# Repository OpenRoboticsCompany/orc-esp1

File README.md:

ESP8266 Development Board
=========================

Front:

Back:

This board provides power, GPIO, and Micro SD to the commonly-available
ESP8266 wifi modules. This first revision is intended for internal use
at Open Robotics Company, but may find it's way out to the world also.

Built using [KiCad EDA](http://kicad.org/)

PCB images courtesy of OSHPark's magical preview.

Important Build Notes
---------------------

Please note that we used a nightly dev build of KiCad for this project.
You cannot open the files in the current stable version (4.0.5 as of this
writing).  We used *kicad-r7402.f631ae2-x86_64* on Windows. It's possible
that later versions will open the files, but because nightly builds are
always changing, you never know!

Copyright
---------

Designed by [Aaron Kondziela](https://aaronkondziela.com).
Copyright 2017 [Open Robotics Company LLC](https://openrobotics.company)

If any files (datasheets, etc) have been included here that are not
our original work, they are (obviously) the copyright of their respective
authors.

License
-------

This work is licensed under a Creative Commons Attribution-ShareAlike 4.0 International License.

https://creativecommons.org/licenses/by-sa/4.0/

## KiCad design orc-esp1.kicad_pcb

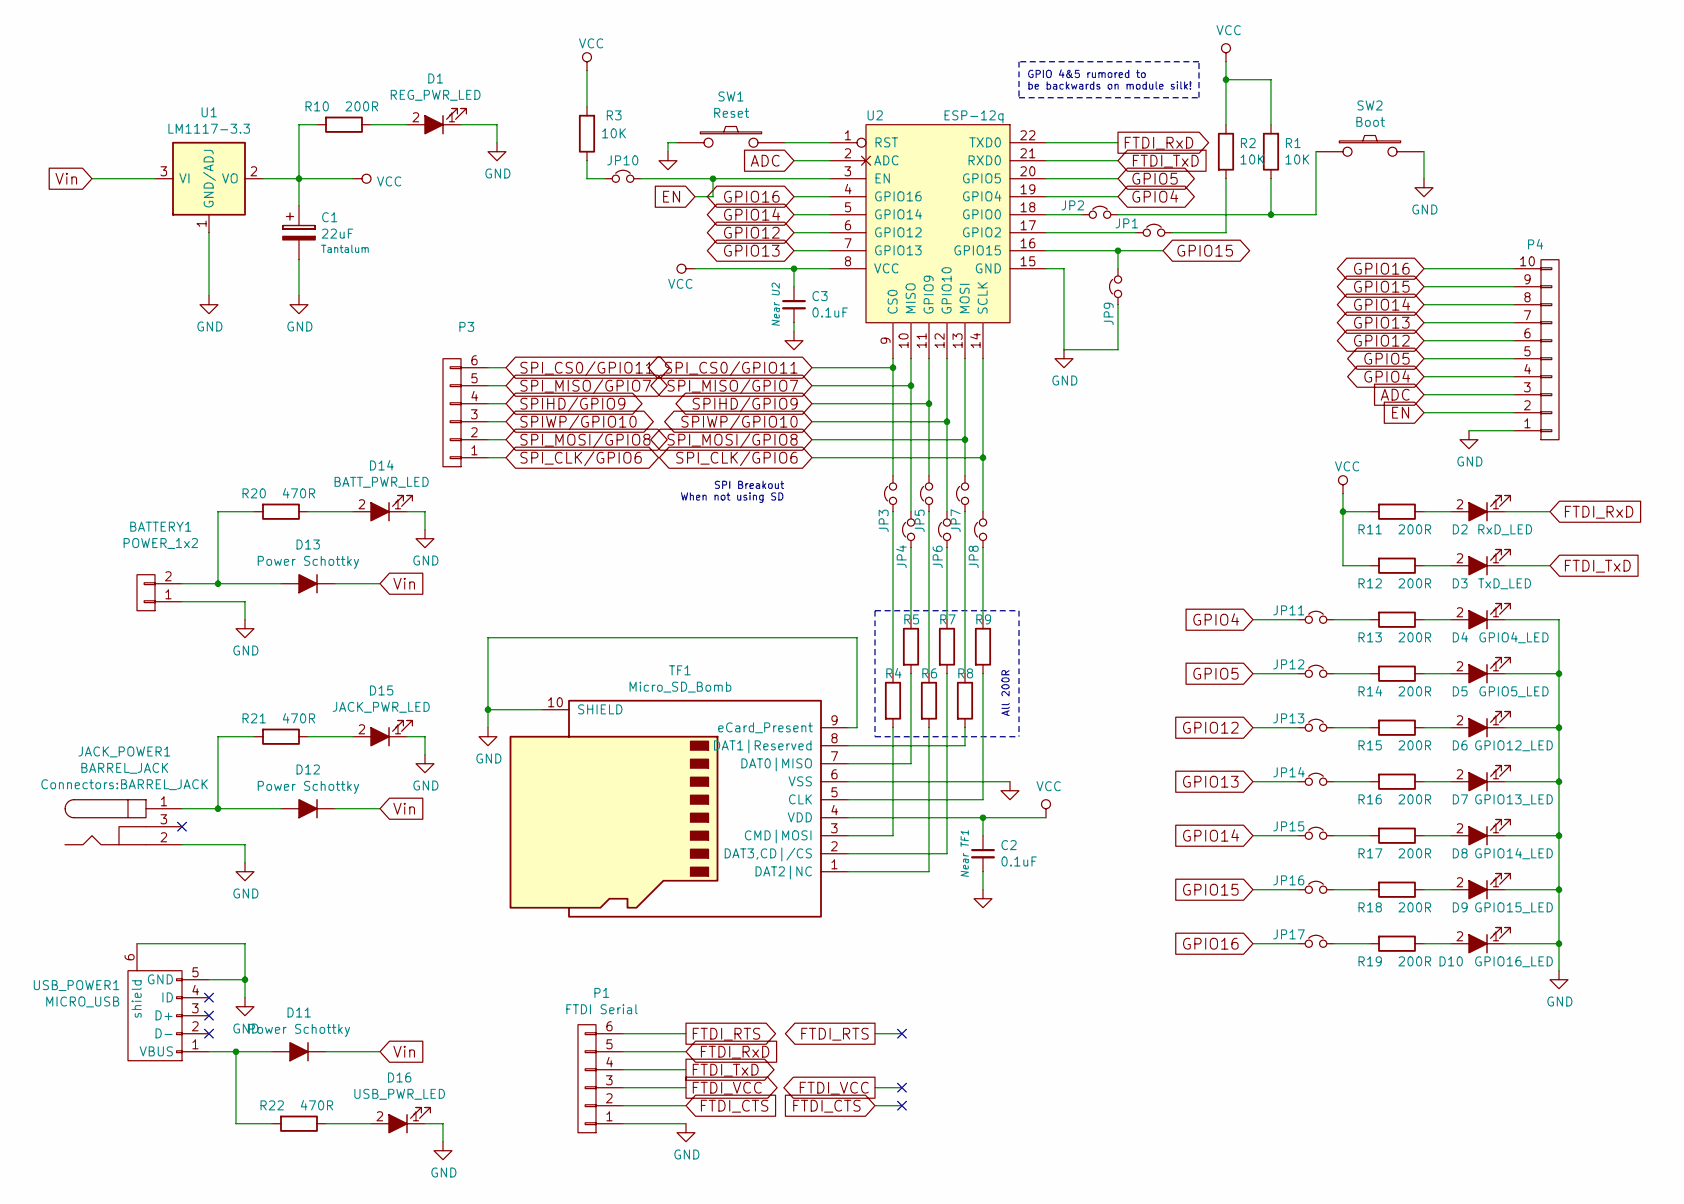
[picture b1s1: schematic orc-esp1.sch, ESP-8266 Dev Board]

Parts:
BATTERY1: POWER_1x2; Pin_Header_Straight_1x02_Pitch2.54mm
C1: 22uF; Tantalum_Case-B_EIA-3528-21_Hand
C2, C3: 0.1uF; C_0603_HandSoldering
D1: REG_PWR_LED; LED_0603
D2: RxD_LED; LED_0603
D3: TxD_LED; LED_0603
D4: GPIO4_LED; LED_0603
D5: GPIO5_LED; LED_0603
D6: GPIO12_LED; LED_0603
D7: GPIO13_LED; LED_0603
D8: GPIO14_LED; LED_0603
D9: GPIO15_LED; LED_0603
D10: GPIO16_LED; LED_0603
D11, D12, D13: Power Schottky; SMB_Handsoldering
D14: BATT_PWR_LED; LED_0603
D15: JACK_PWR_LED; LED_0603
D16: USB_PWR_LED; LED_0603
JACK_POWER1: BARREL_JACK
JP1: BOOT_JP3; Jumper_1206_NC_DNP
JP2: BOOT_JP; Jumper_1206_NC_DNP
JP3: SD_JP3; Jumper_1206_NC_DNP
JP4: SD_JP4; Jumper_1206_NC_DNP
JP5: SD_JP5; Jumper_1206_NC_DNP
JP6: SD_JP6; Jumper_1206_NC_DNP
JP7: SD_JP7; Jumper_1206_NC_DNP
JP8: SD_JP8; Jumper_1206_NC_DNP
JP9: BOOT_JP2; Jumper_1206_NC_DNP
JP10: EN_JP; Jumper_1206_NC_DNP
JP11: GPIO4_JP; Pin_Header_Straight_1x02
JP12: GPIO5_JP; Pin_Header_Straight_1x02
JP13: GPIO12_JP; Pin_Header_Straight_1x02
JP14: GPIO13_JP; Pin_Header_Straight_1x02
JP15: GPIO14_JP; Pin_Header_Straight_1x02
JP16: GPIO15_JP; Pin_Header_Straight_1x02
JP17: GPIO16_JP; Pin_Header_Straight_1x02
P1: FTDI Serial; Pin_Header_Straight_1x06_Pitch2.54mm
P3: CONN_01X06; Pin_Header_Straight_1x06
P4: CONN_01X10; Pin_Header_Straight_1x10
R1, R2, R3: 10K; R_0603_HandSoldering
R4, R5, R6, R7, R8, R9, R10, R11, R12, R13, R14, R15, R16, R17, R18, R19: 200R; R_0603_HandSoldering
R20, R21, R22: 470R; R_0603_HandSoldering
SW1: Reset; SW_PUSH_6mm
SW2: Boot; SW_PUSH_6mm
TF1: Micro_SD_Bomb; Sumai-Micro-SD-Bomb
U1: LM1117-3.3; SOT-223
U2: ESP-12q; ESP-12-Q
USB_POWER1: MICRO_USB; USB_Micro-B

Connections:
ADC: P4.3, U2.2 (ADC)
EN: JP10.2, P4.2, U2.3 (EN)
FTDI_CTS: P1.2
FTDI_RTS: P1.6
FTDI_RxD: D2.1 (K), P1.5, U2.22 (TXD0)
FTDI_TxD: D3.1 (K), P1.4, U2.21 (RXD0)
FTDI_VCC: P1.3
GND: BATTERY1.1 (eeGND), C1.2, C2.2, C3.2, D1.1 (K), D4.1 (K), D5.1 (K), D6.1 (K), D7.1 (K), D8.1 (K), D9.1 (K), D10.1 (K), D14.1 (K), D15.1 (K), D16.1 (K), JACK_POWER1.2, JACK_POWER1.3, JP9.1, P1.1, P4.1, SW1.1, SW2.2, TF1.6 (VSS), TF1.9 (eCard_Present), TF1.10 (SHIELD), U1.1 (GND/ADJ), U2.15 (GND), USB_POWER1.5 (GND), USB_POWER1.6 (shield); also elsewhere on the board
GPIO4: JP11.1, P4.4, U2.19 (GPIO4)
GPIO5: JP12.1, P4.5, U2.20 (GPIO5)
GPIO12: JP13.1, P4.6, U2.6 (GPIO12)
GPIO13: JP14.1, P4.7, U2.7 (GPIO13)
GPIO14: JP15.1, P4.8, U2.5 (GPIO14)
GPIO15: JP9.2, JP16.1, P4.9, U2.16 (GPIO15)
GPIO16: JP17.1, P4.10, U2.4 (GPIO16)
unnamed: BATTERY1.2 (+BAT), D13.2 (A), R20.2
unnamed: D1.2 (A), R10.1
unnamed: D2.2 (A), R11.1
unnamed: D3.2 (A), R12.1
unnamed: D4.2 (A), R13.1
unnamed: D5.2 (A), R14.1
unnamed: D6.2 (A), R15.1
unnamed: D7.2 (A), R16.1
unnamed: D8.2 (A), R17.1
unnamed: D9.2 (A), R18.1
unnamed: D10.2 (A), R19.1
unnamed: D11.2 (A), R22.2, USB_POWER1.1 (VBUS)
unnamed: D12.2 (A), JACK_POWER1.1, R21.2
unnamed: D14.2 (A), R20.1
unnamed: D15.2 (A), R21.1
unnamed: D16.2 (A), R22.1
unnamed: JP1.1, U2.17 (GPIO2)
unnamed: JP1.2, R2.2
unnamed: JP2.1, U2.18 (GPIO0)
unnamed: JP2.2, R1.1, SW2.1
unnamed: JP3.1, R4.1
unnamed: JP4.1, R5.1
unnamed: JP5.1, R6.1
unnamed: JP6.1, R7.1
unnamed: JP7.1, R8.1
unnamed: JP8.1, R9.1
unnamed: JP10.1, R3.1
unnamed: JP11.2, R13.2
unnamed: JP12.2, R14.2
unnamed: JP13.2, R15.2
unnamed: JP14.2, R16.2
unnamed: JP15.2, R17.2
unnamed: JP16.2, R18.2
unnamed: JP17.2, R19.2
unnamed: R4.2, TF1.3 (CMD|MOSI)
unnamed: R5.2, TF1.7 (DAT0|MISO)
unnamed: R6.2, TF1.1 (DAT2|NC)
unnamed: R7.2, TF1.2 (DAT3,CD|/CS)
unnamed: R8.2, TF1.8 (DAT1|Reserved)
unnamed: R9.2, TF1.5 (CLK)
unnamed: SW1.2, U2.1 (RST)
SPIHD/GPIO9: JP5.2, P3.4, U2.11 (GPIO9)
SPIWP/GPIO10: JP6.2, P3.3, U2.12 (GPIO10)
SPI_CLK/GPIO6: JP8.2, P3.1, U2.14 (SCLK)
SPI_CS0/GPIO11: JP3.2, P3.6, U2.9 (CS0)
SPI_MISO/GPIO7: JP4.2, P3.5, U2.10 (MISO)
SPI_MOSI/GPIO8: JP7.2, P3.2, U2.13 (MOSI)
VCC: C1.1, C2.1, C3.1, R1.2, R2.1, R3.2, R10.2, R11.2, R12.2, TF1.4 (VDD), U1.2 (VO), U1.4 (VO), U2.8 (VCC)
Vin: D11.1 (K), D12.1 (K), D13.1 (K), U1.3 (VI)

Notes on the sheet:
GPIO 4&5 rumored to be backwards on module silk!
All 200R
SPI Breakout When not using SD

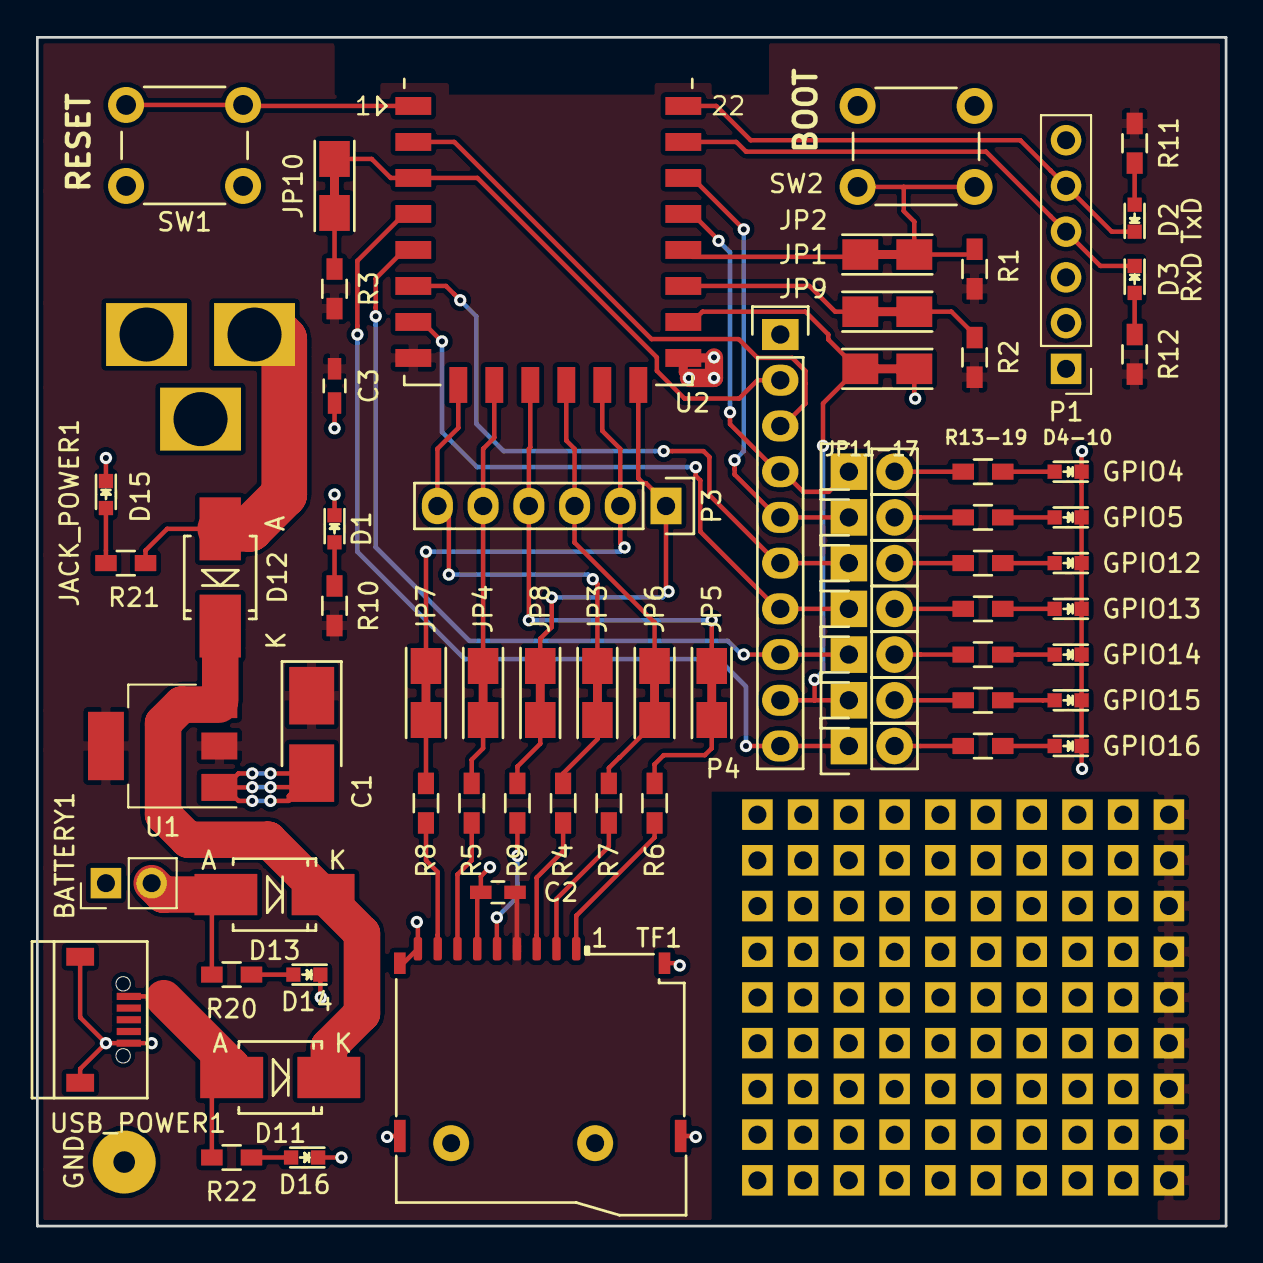
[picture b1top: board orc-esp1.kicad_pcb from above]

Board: 2 copper layers, 66.0 x 66.0 mm, 70 parts (0 on the bottom side), 61 nets.

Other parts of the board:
GND: GND; SolderWirePad_single_1-2mmDrill

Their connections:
GND: GND.1; also elsewhere on the board

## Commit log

2017-03-01 ESP8266 dev board
2021-11-10 Update README.md
    https://forum.kicad.info/t/warning-avoid-all-links-to-kicad-pcb-org-use-kicad-org/31521

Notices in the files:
orc-esp1.kicad_pcb:
(C)2017 Open Robotics Company LLC
orc-esp1.sch:
Copyright 2016 Open Robotics Company LLC
